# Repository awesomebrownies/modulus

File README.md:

# Modulus
Modulus is a continuation of my journey within hack club's YSWS hackpad v2. This board features **reversible** PCB's, saving on cost. It has a **separated thumb cluster** utilizing **ribbon cables** and a column stagger layout allowing for ergonomic hand placement. It also includes motors for **haptic feedback**, allowing main row modifiers to be used easily.

The reasoning behind this creation is I wanted a keyboard with a comfortable thumb cluster. Typically a keyboard of this type costs hundreds of dollars to make (though it doesn't have a trackball). I wanted something custom and fun, but at a much lower budget. One of my previous keyboards used main row modifiers without a notification. This version includes motors for haptic feedback, improving user experience.

A couple of tips to putting this together. For the thumb cluster PCB, solder the bridges on the top side where the microcontroller is mounted for proper functionality. Other than that, you just need to connect the ribbon cable and everything else is standard for setting up any other ergo keyboard.

## Bill of Materials

<table>
  <thead>
    <tr>
      <th>Category</th>
      <th>Item Description</th>
      <th>Vendor</th>
      <th>Price</th>
      <th>Shipping</th>
      <th>Total</th>
      <th>Link</th>
    </tr>
  </thead>
  <tbody>
    <tr>
      <td><strong>Microcontrollers</strong></td>
      <td>2x Orpheus Pico's or Raspberry Pi Picos</td>
      <td>Aliexpress</td>
      <td>$8.00</td>
      <td>Free</td>
      <td><strong>$8.00</strong></td>
      <td><a href="https://vilros.com/products/raspberry-pi-pico">Link</a></td>
    </tr>
    <tr>
      <td><strong>Switches</strong></td>
      <td>45 pcs Rosewood Akko Switches</td>
      <td>Amazon</td>
      <td>$16.99</td>
      <td>Free</td>
      <td><strong>$16.99</strong></td>
      <td><a href="https://www.amazon.com/Akko-Rosewood-Keyboard-Mechanical-Pre-Lubed/dp/B0D7VG2QJH?th=1">Link</a></td>
    </tr>
    <tr>
      <td><strong>Keycaps</strong></td>
      <td>Honey Milk Keycaps (Keycap set)</td>
      <td>Amazon</td>
      <td>$22.00</td>
      <td>Free</td>
      <td><strong>$22.00</strong></td>
      <td><a href="https://www.amazon.com/Keycaps-Minimalist-Compatible-Mechanical-Keyboards/dp/B0948XRKCQ/">Link</a></td>
    </tr>
    <tr>
      <td rowspan="3"><strong>Electronic Components</strong></td>
      <td>Kailh Hotswap Socket</td>
      <td>AliExpress</td>
      <td>$6.42</td>
      <td>Free</td>
      <td rowspan="3"><strong>$14.27</strong></td>
      <td><a href="https://www.aliexpress.us/item/3256803389452947.html">Link</a></td>
    </tr>
    <tr>
      <td>Mini Motor Disc</td>
      <td>Aliexpress</td>
      <td>$3.31</td>
      <td>$3.00</td>
      <td><a href="https://www.aliexpress.us/item/3256806157955199.html?spm=a2g0o.tesla.0.0.fe7c9CIp9CIpCx&afTraceInfo=1005006344269951__pc__c_ppc_item_bridge_pc_main__ZC5eIQh__1759903786749&gatewayAdapt=glo2usa4itemAdapt">Link</a></td>
    </tr>
    <tr>
      <td>SOD-123 Diode</td>
      <td>Aliexpress</td>
      <td>$1.54</td>
      <td>Free</td>
      <td><a href="https://www.aliexpress.us/item/2251832693131413.html">Link</a></td>
    </tr>
    <tr>
      <td rowspan="2"><strong>Grant</strong></td>
      <td>2x PCB</td>
      <td>JLCPCB</td>
      <td>$14.26</td>
      <td>$14.14</td>
      <td rowspan="2"><strong>$32.03</strong></td>
      <td>N/A</td>
    </tr>
    <tr>
      <td>Ribbon Cable</td>
      <td>AliExpress</td>
      <td>$1.45</td>
      <td>$1.99</td>
      <td><a href="https://www.aliexpress.us/item/3256807375022913.html">Link</a></td>
    </tr>
  </tbody>
</table>

TOTAL: ~$89 (Depending on choice item selection)

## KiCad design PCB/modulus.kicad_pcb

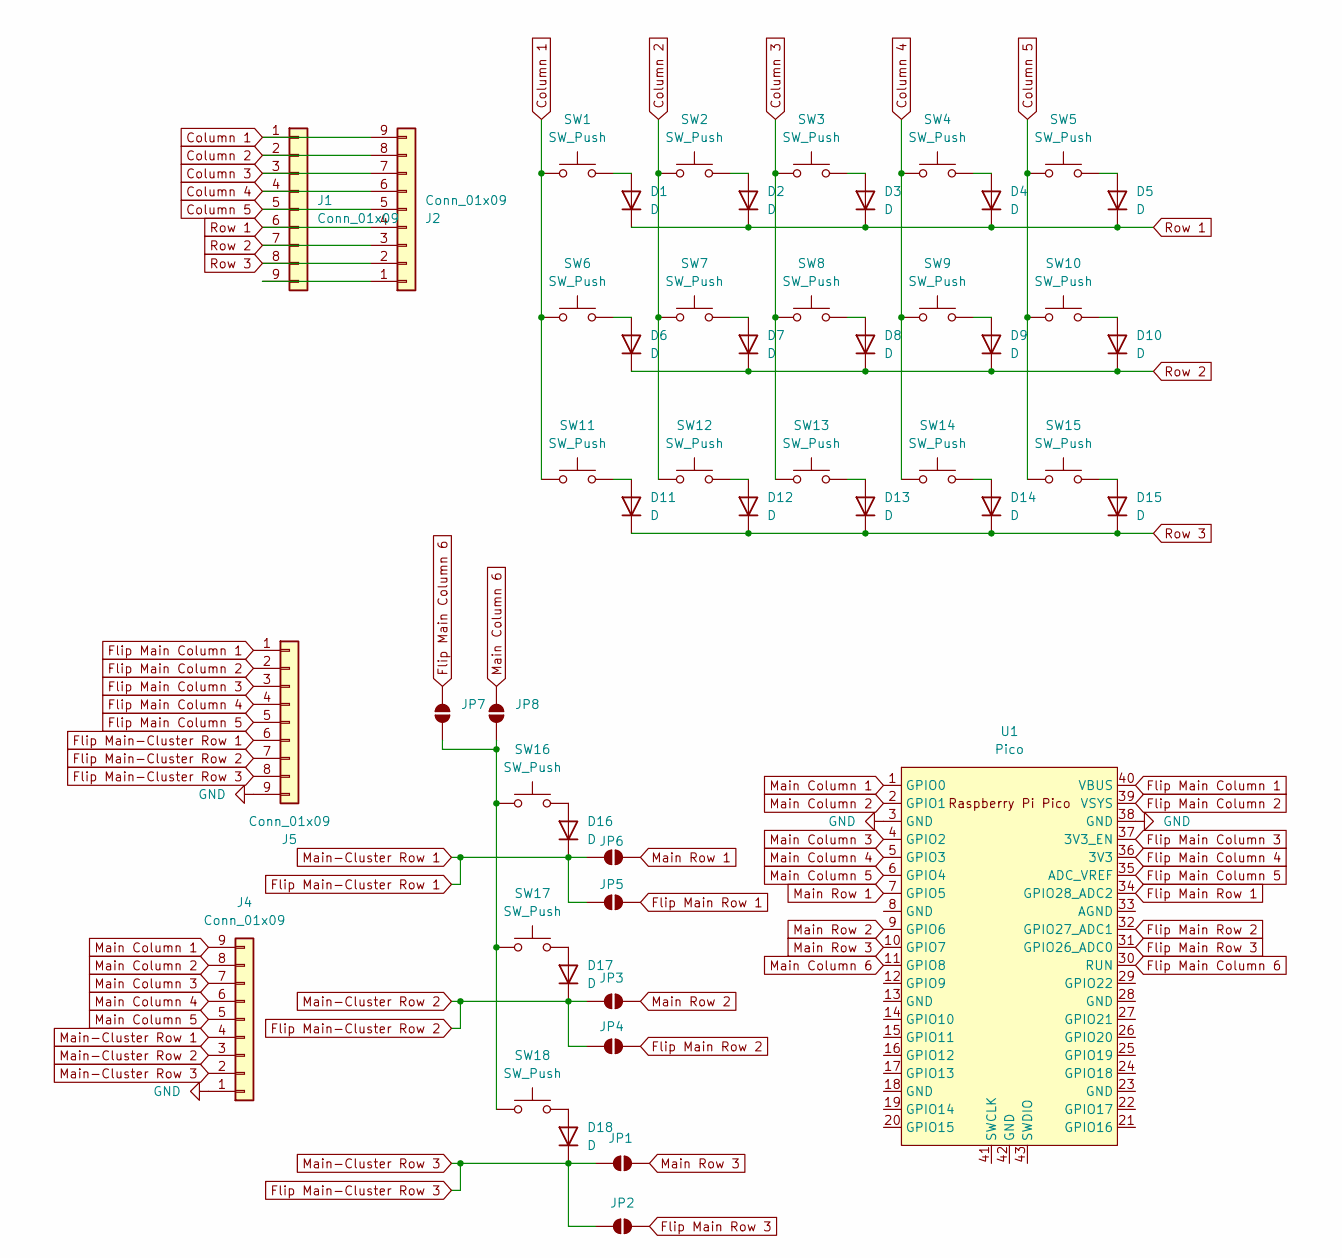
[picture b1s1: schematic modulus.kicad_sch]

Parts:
D1, D2, D3, D4, D5, D6, D7, D8, D9, D10, D11, D12, D13, D14, D15, D16, D17, D18: D; D3_SMD
J1, J2, J4, J5: Conn_01x09; Molex_200528-0090_1x09-1MP_P1.00mm_Horizontal
JP1, JP2, JP3, JP4, JP5, JP6, JP7, JP8: SolderJumper_2_Open; SolderJumper-2_P1.3mm_Open_TrianglePad1.0x1.5mm
SW1, SW2, SW3, SW4, SW5, SW6, SW7, SW8, SW9, SW10, SW11, SW12, SW13, SW14, SW15, SW16, SW17, SW18: SW_Push; Kailh_socket_MX_reversible
U1: Pico; RPi_Pico_SMD_TH

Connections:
Column 1: J1.1, J2.9, SW1.1, SW6.1, SW11.1
Column 2: J1.2, J2.8, SW2.1, SW7.1, SW12.1
Column 3: J1.3, J2.7, SW3.1, SW8.1, SW13.1
Column 4: J1.4, J2.6, SW4.1, SW9.1, SW14.1
Column 5: J1.5, J2.5, SW5.1, SW10.1, SW15.1
Flip Main Column 1: J5.1, U1.40 (VBUS)
Flip Main Column 2: J5.2, U1.39 (VSYS)
Flip Main Column 3: J5.3, U1.37 (3V3_EN)
Flip Main Column 4: J5.4, U1.36 (3V3)
Flip Main Column 5: J5.5, U1.35 (ADC_VREF)
Flip Main Column 6: JP7.2 (B), U1.30 (RUN)
Flip Main Row 1: JP5.2 (B), U1.34 (GPIO28_ADC2)
Flip Main Row 2: JP4.2 (B), U1.32 (GPIO27_ADC1)
Flip Main Row 3: JP2.2 (B), U1.31 (GPIO26_ADC0)
Flip Main-Cluster Row 1: D16.1 (K), J4.4, J5.6, JP5.1 (A), JP6.1 (A)
Flip Main-Cluster Row 2: D17.1 (K), J4.3, J5.7, JP3.1 (A), JP4.1 (A)
Flip Main-Cluster Row 3: D18.1 (K), J4.2, J5.8, JP1.1 (A), JP2.1 (A)
GND: J4.1, J5.9, U1.3 (GND), U1.38 (GND)
Main Column 1: J4.9, U1.1 (GPIO0)
Main Column 2: J4.8, U1.2 (GPIO1)
Main Column 3: J4.7, U1.4 (GPIO2)
Main Column 4: J4.6, U1.5 (GPIO3)
Main Column 5: J4.5, U1.6 (GPIO4)
Main Column 6: JP8.2 (B), U1.11 (GPIO8)
Main Row 1: JP6.2 (B), U1.7 (GPIO5)
Main Row 2: JP3.2 (B), U1.9 (GPIO6)
Main Row 3: JP1.2 (B), U1.10 (GPIO7)
unnamed: D1.2 (A), SW1.2
unnamed: D2.2 (A), SW2.2
unnamed: D3.2 (A), SW3.2
unnamed: D4.2 (A), SW4.2
unnamed: D5.2 (A), SW5.2
unnamed: D6.2 (A), SW6.2
unnamed: D7.2 (A), SW7.2
unnamed: D8.2 (A), SW8.2
unnamed: D9.2 (A), SW9.2
unnamed: D10.2 (A), SW10.2
unnamed: D11.2 (A), SW11.2
unnamed: D12.2 (A), SW12.2
unnamed: D13.2 (A), SW13.2
unnamed: D14.2 (A), SW14.2
unnamed: D15.2 (A), SW15.2
unnamed: D16.2 (A), SW16.2
unnamed: D17.2 (A), SW17.2
unnamed: D18.2 (A), SW18.2
unnamed: J1.9, J2.1
unnamed: JP7.1 (A), JP8.1 (A), SW16.1, SW17.1, SW18.1
Row 1: D1.1 (K), D2.1 (K), D3.1 (K), D4.1 (K), D5.1 (K), J1.6, J2.4
Row 2: D6.1 (K), D7.1 (K), D8.1 (K), D9.1 (K), D10.1 (K), J1.7, J2.3
Row 3: D11.1 (K), D12.1 (K), D13.1 (K), D14.1 (K), D15.1 (K), J1.8, J2.2

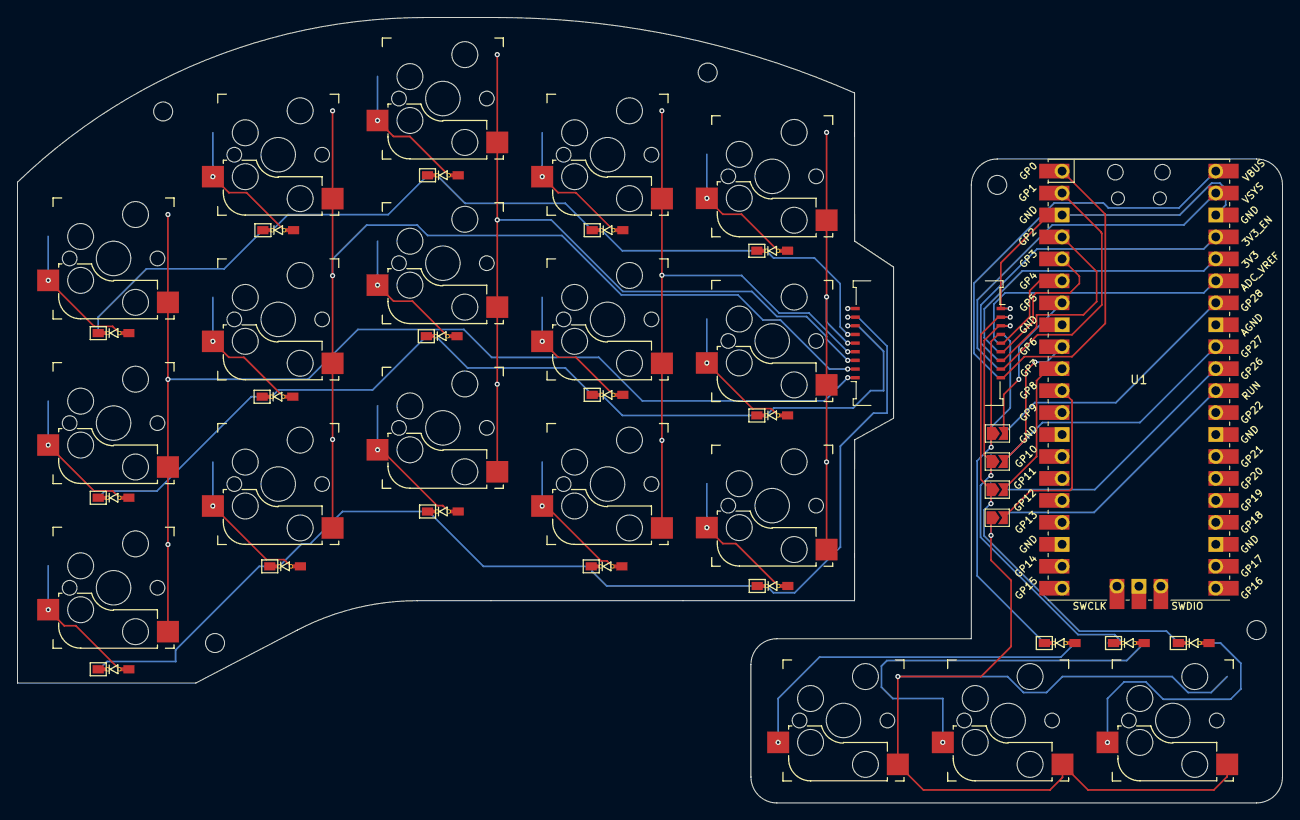
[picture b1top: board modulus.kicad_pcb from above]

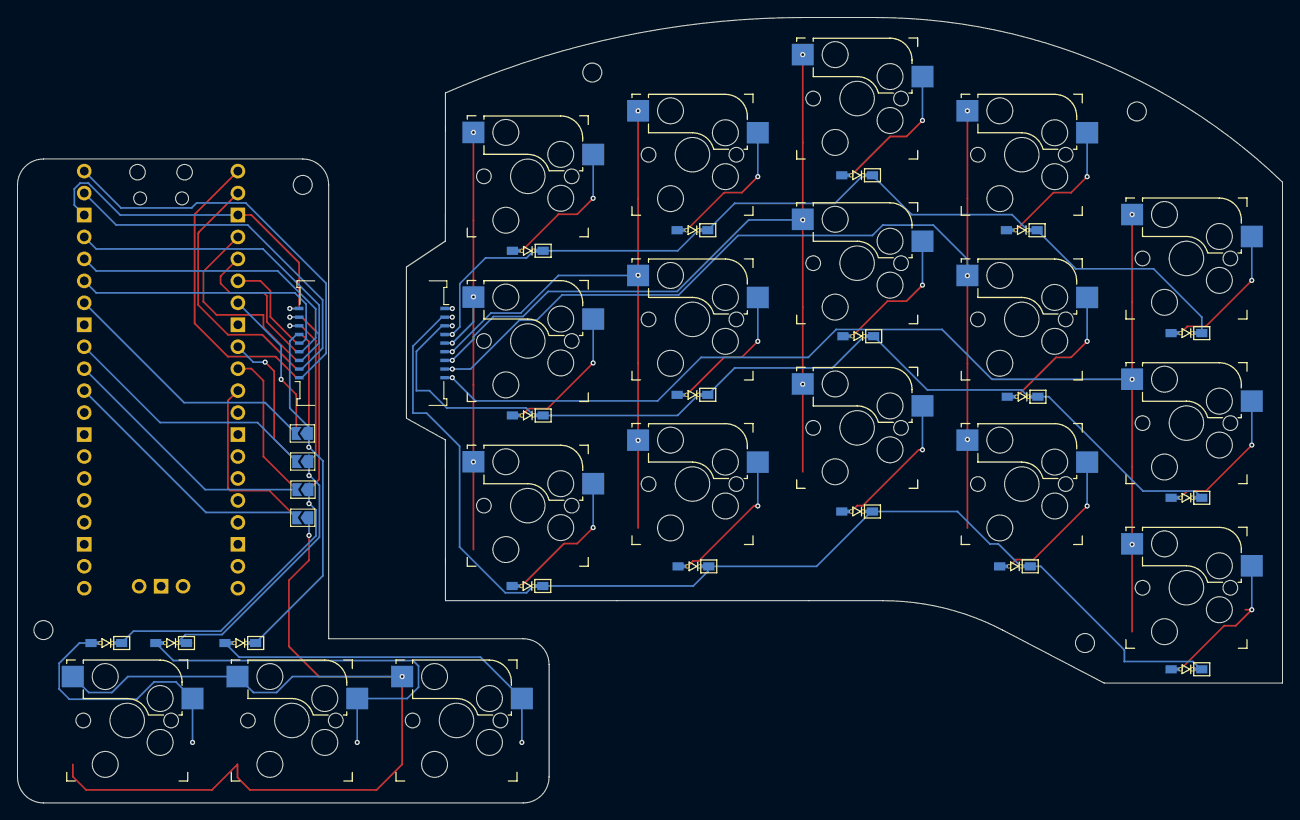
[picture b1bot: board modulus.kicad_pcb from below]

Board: 2 copper layers, 146.3 x 90.9 mm, 49 parts (6 on the bottom side), 50 nets.

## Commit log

2025-03-15 Add modulus files
2025-03-24 Remove libraries
2025-03-24 Reformat structure
2025-03-24 Add latest PCB version
2025-03-24 Relocate files
2025-06-05 Update from M3 to M2 holes
2025-06-06 Add 3d print files
2025-06-06 Minimize thumb cluster
2025-06-06 Add qmk keymap
